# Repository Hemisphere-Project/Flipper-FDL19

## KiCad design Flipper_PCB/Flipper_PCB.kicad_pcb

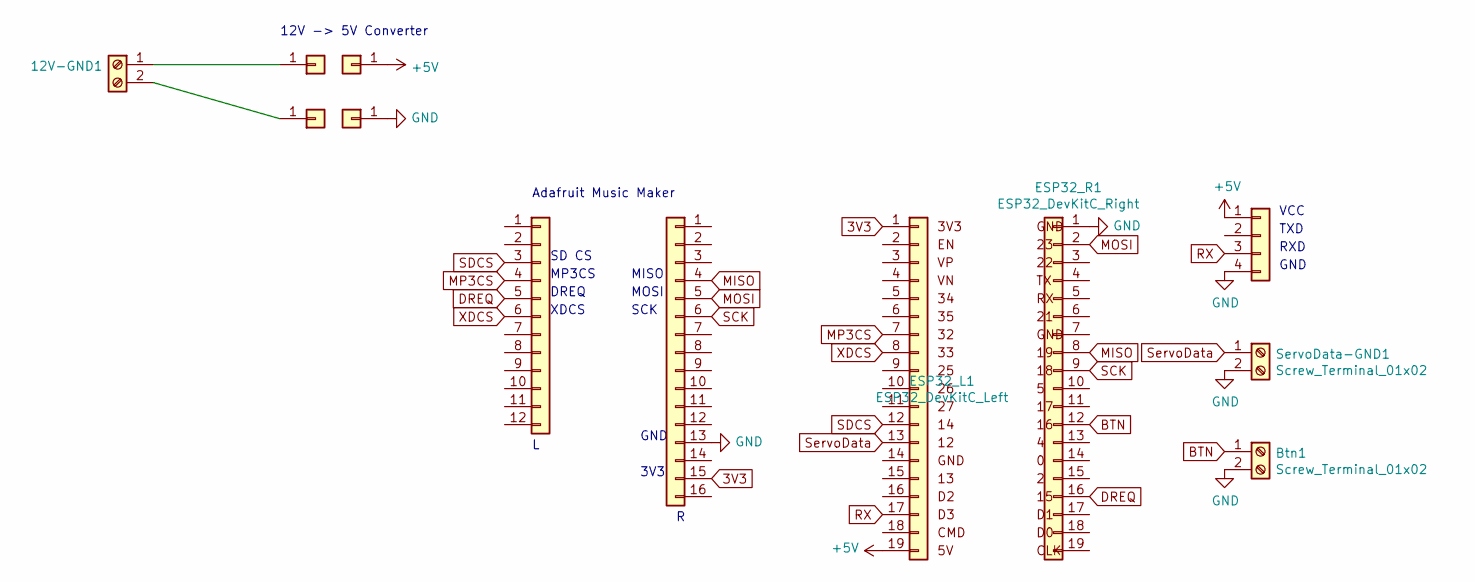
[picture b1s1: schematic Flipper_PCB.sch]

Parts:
5V1, 12V1: Conn_01x01; PinHeader_1x01_P2.54mm_Vertical
12V-GND1: Screw_Terminal_01x02; TerminalBlock_bornier-2_P5.08mm
Btn1: Screw_Terminal_01x02; TerminalBlock_bornier-2_P5.08mm
ESP32_L1: ESP32_DevKitC_Left; PinSocket_1x19_P2.54mm_Vertical
ESP32_R1: ESP32_DevKitC_Right; PinSocket_1x19_P2.54mm_Vertical
GND1, GND2: Conn_01x01; PinHeader_1x01_P2.54mm_Vertical
MusicMaker_Left1: Conn_01x12; PinSocket_1x12_P2.54mm_Vertical
MusicMaker_Right1: Conn_01x16; PinSocket_1x16_P2.54mm_Vertical
SERIAL1: Conn_01x04; PinSocket_1x04_P2.54mm_Vertical
ServoData-GND1: Screw_Terminal_01x02; TerminalBlock_bornier-2_P5.08mm

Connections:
3V3: ESP32_L1.1, MusicMaker_Right1.15
+5V: 5V1.1, ESP32_L1.19, SERIAL1.1
BTN: Btn1.1, ESP32_R1.12
DREQ: ESP32_R1.16, MusicMaker_Left1.5
GND: Btn1.2, ESP32_R1.1, GND2.1, MusicMaker_Right1.13, SERIAL1.4, ServoData-GND1.2
MISO: ESP32_R1.8, MusicMaker_Right1.4
MOSI: ESP32_R1.2, MusicMaker_Right1.5
MP3CS: ESP32_L1.7, MusicMaker_Left1.4
unnamed: 12V1.1, 12V-GND1.1
unnamed: 12V-GND1.2, GND1.1
RX: ESP32_L1.17, SERIAL1.3
SCK: ESP32_R1.9, MusicMaker_Right1.6
SDCS: ESP32_L1.12, MusicMaker_Left1.3
ServoData: ESP32_L1.13, ServoData-GND1.1
XDCS: ESP32_L1.8, MusicMaker_Left1.6

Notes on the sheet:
MISO
MOSI
SCK
SD CS
MP3CS
DREQ
XDCS
Adafruit Music Maker
VCC
TXD
RXD
GND
12V -> 5V Converter
3V3

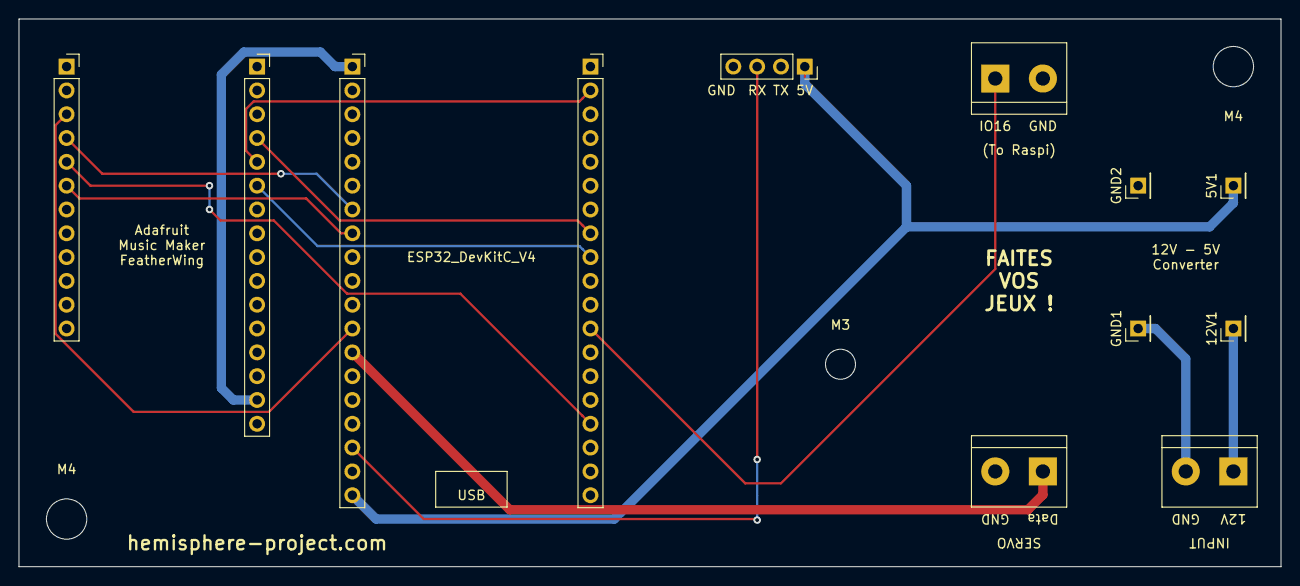
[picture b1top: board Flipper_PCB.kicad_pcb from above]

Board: 2 copper layers, 134.6 x 58.4 mm, 15 parts (0 on the bottom side), 15 nets.

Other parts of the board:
M3: MountingHole_3.2mm_M3
M4, M4#2: MountingHole_4.3mm_M4

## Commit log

2019-11-06 init
2019-11-14 pcb ready
2019-11-22 motor
2019-11-25 out of array actions ok
2019-11-25 playing conflict ok
2019-11-25 bt params
2019-11-25 testeur
2019-11-26 tester ok w push data
2019-11-26 stop before play
2019-11-26 motor double
2019-11-27 expl
2019-11-27 bug moteur
2019-11-27 fade out end ok
2019-11-28 motor 2nd core
2019-11-28 br > m
2019-11-28 jeudi
2019-11-29 last v
2019-11-29 seems ok !
